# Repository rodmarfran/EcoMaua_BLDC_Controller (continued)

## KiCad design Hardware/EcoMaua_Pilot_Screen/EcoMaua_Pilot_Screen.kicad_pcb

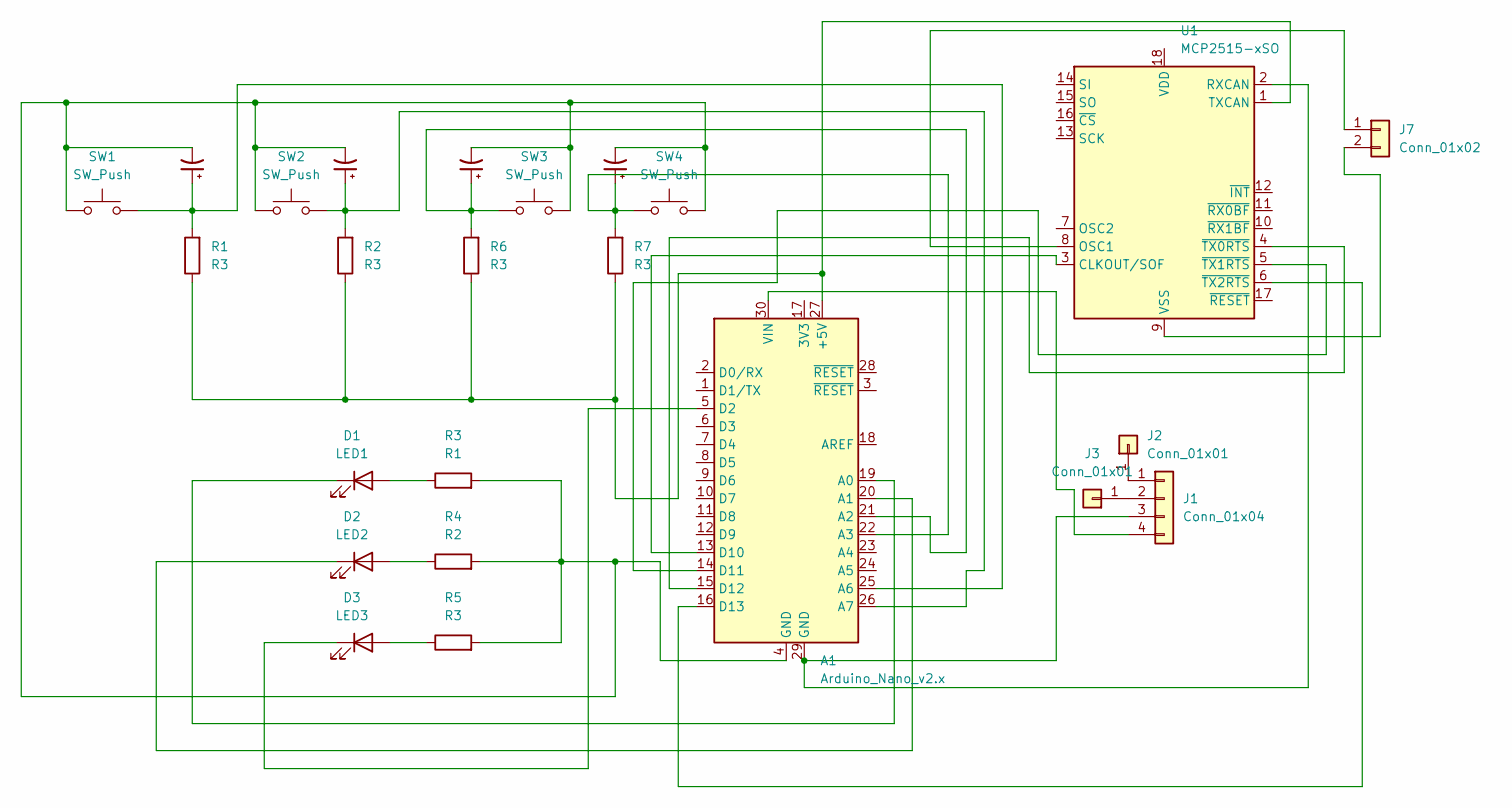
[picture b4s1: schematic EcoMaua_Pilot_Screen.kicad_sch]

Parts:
A1: Arduino_Nano_v2.x; Arduino_Nano
C1, C2, C3, C4: C_Polarized_Small_US; CP_Radial_D5.0mm_P2.50mm
D1: LED1; LED_D3.0mm
D2: LED2; LED_D3.0mm
D3: LED3; LED_D3.0mm
J1: Conn_01x04; LM2596 DC-DC HW-411
J2, J3: Conn_01x01; SolderWire-0.25sqmm_1x01_D0.65mm_OD2mm
J7: Conn_01x02; SolderWire-0.25sqmm_1x02_P4.2mm_D0.65mm_OD1.7mm
R1, R2, R5, R6, R7: R3; R_Axial_DIN0207_L6.3mm_D2.5mm_P10.16mm_Horizontal
R3: R1; R_Axial_DIN0207_L6.3mm_D2.5mm_P10.16mm_Horizontal
R4: R2; R_Axial_DIN0207_L6.3mm_D2.5mm_P10.16mm_Horizontal
SW1, SW2, SW3, SW4: SW_Push; SW_DIP_SPSTx01_Piano_10.8x4.1mm_W7.62mm_P2.54mm
U1: MCP2515-xSO; MCP2515-CANBUS MODULE FOOTPRINT

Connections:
unnamed: A1.27 (+5V), R1.1, R2.1, R6.1, R7.1, U1.1 (TXCAN)
unnamed: A1.19 (A0), D1.1 (K)
unnamed: A1.20 (A1), D2.1 (K)
unnamed: A1.21 (A2), C3.1, R6.2, SW3.1
unnamed: A1.22 (A3), C4.1, R7.2, SW4.1
unnamed: A1.25 (A6), C1.1, R1.2, SW1.2
unnamed: A1.26 (A7), C2.1, R2.2, SW2.2
unnamed: A1.5 (D2), D3.1 (K)
unnamed: A1.13 (D10), U1.3 (CLKOUT/SOF)
unnamed: A1.14 (D11), U1.5 (~TX1RTS)
unnamed: A1.15 (D12), U1.4 (~TX0RTS)
unnamed: A1.16 (D13), U1.6 (~TX2RTS)
unnamed: A1.4 (GND), C1.2, C2.2, C3.2, C4.2, R3.2, R4.2, R5.2, SW1.1, SW2.1, SW3.2, SW4.2
unnamed: A1.30 (VIN), J1.4
unnamed: D1.2 (A), R3.1
unnamed: D2.2 (A), R4.1
unnamed: D3.2 (A), R5.1
unnamed: J1.1, J2.1
unnamed: J1.2, J3.1
unnamed: A1.29 (GND), J1.3, U1.2 (RXCAN)
unnamed: J7.1, U1.8 (OSC1)
unnamed: J7.2, U1.9 (VSS)

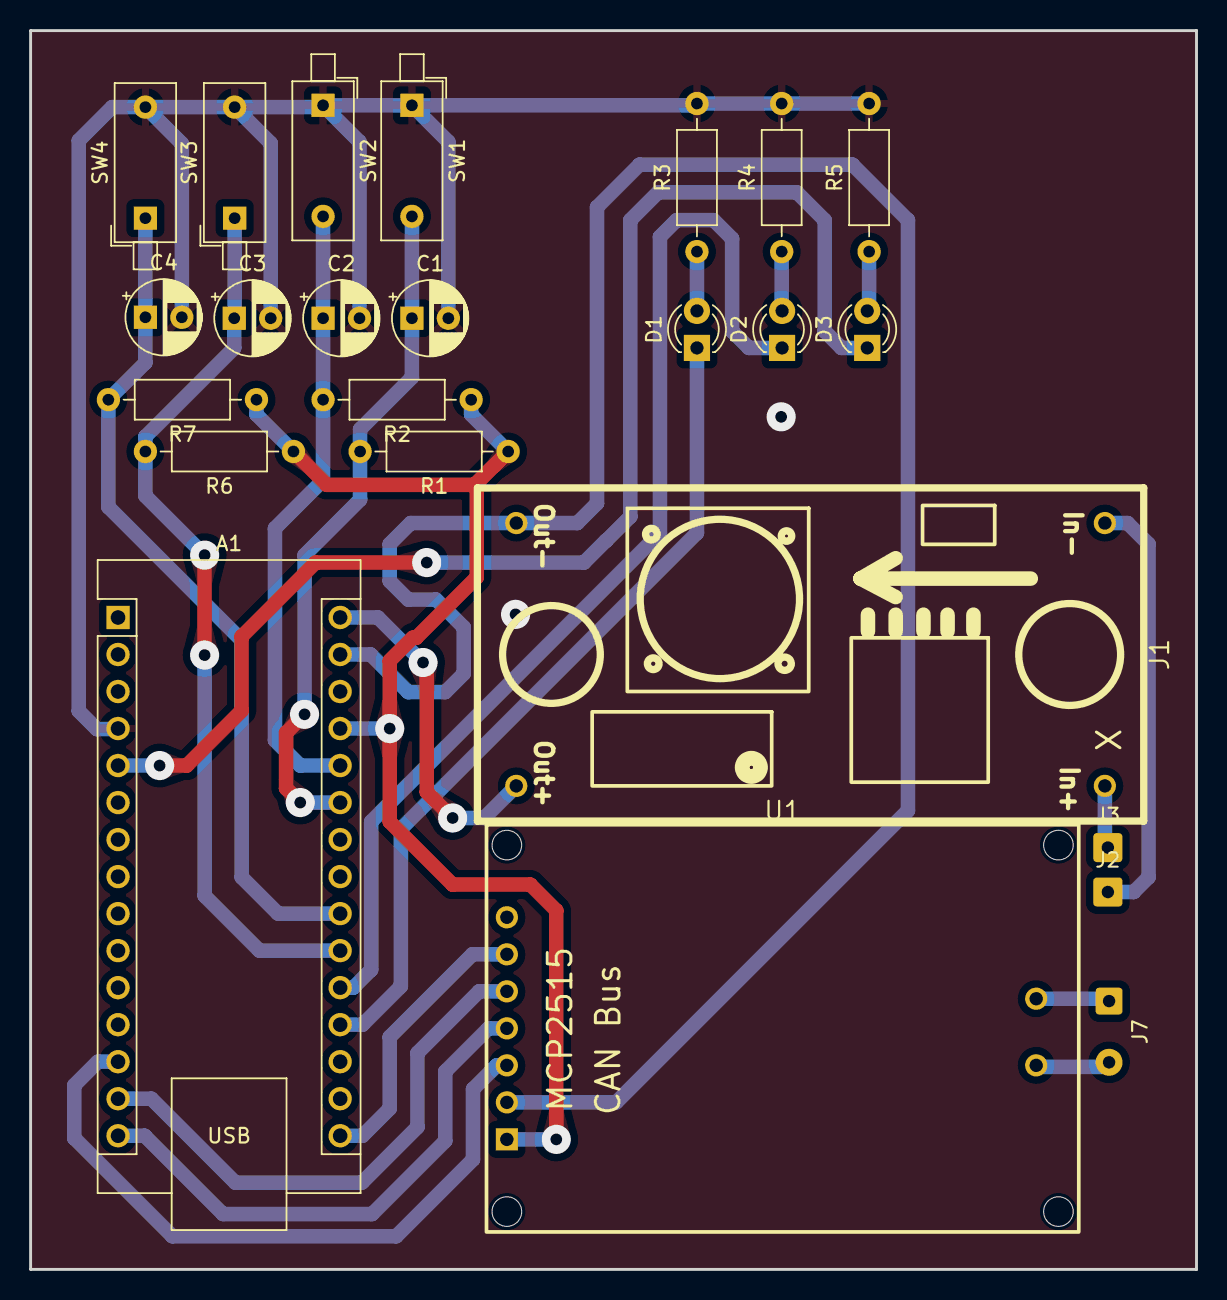
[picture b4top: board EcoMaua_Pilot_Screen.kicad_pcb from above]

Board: 2 copper layers, 80.0 x 85.0 mm, 24 parts (0 on the bottom side), 22 nets.

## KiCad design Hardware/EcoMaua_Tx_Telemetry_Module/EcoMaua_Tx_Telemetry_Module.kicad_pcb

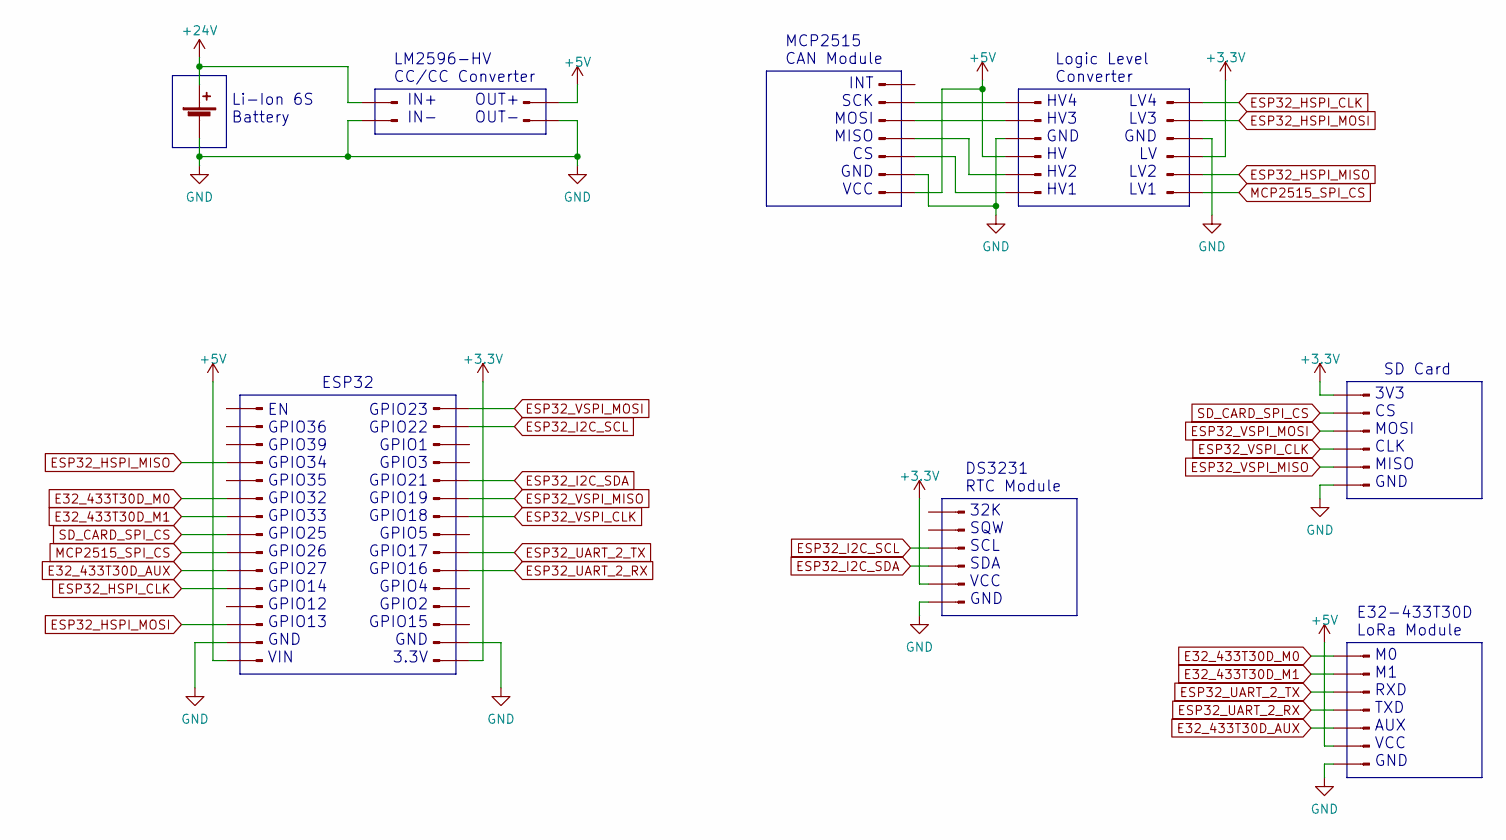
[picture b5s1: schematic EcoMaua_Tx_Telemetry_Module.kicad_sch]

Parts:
BT1: Li-Ion 6S Battery; PinHeader_1x02_P2.54mm_Vertical
J1, J3: Conn_01x15_Pin; PinHeader_1x15_P2.54mm_Vertical
J2, J4: Conn_01x02_Pin; PinHeader_1x02_P2.54mm_Vertical
J5, J10: Conn_01x07_Pin; PinSocket_1x07_P2.54mm_Vertical
J6, J7, J8, J9: Conn_01x06_Pin; PinHeader_1x06_P2.54mm_Vertical

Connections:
+3.3V: J3.15, J6.2, J8.4, J9.6
+5V: J1.1, J4.1, J5.7, J7.3, J10.2
+24V: BT1.1 (+), J2.2
E32_433T30D_AUX: J1.6, J10.3
E32_433T30D_M0: J1.10, J10.7
E32_433T30D_M1: J1.9, J10.6
ESP32_HSPI_CLK: J1.5, J8.1
ESP32_HSPI_MISO: J1.12, J8.5
ESP32_HSPI_MOSI: J1.3, J8.2
ESP32_I2C_SCL: J3.2, J6.4
ESP32_I2C_SDA: J3.5, J6.3
ESP32_UART_2_RX: J3.10, J10.4
ESP32_UART_2_TX: J3.9, J10.5
ESP32_VSPI_CLK: J3.7, J9.3
ESP32_VSPI_MISO: J3.6, J9.2
ESP32_VSPI_MOSI: J3.1, J9.4
GND: BT1.2 (-), J1.2, J2.1, J3.14, J4.2, J5.6, J6.1, J7.4, J8.3, J9.1, J10.1
MCP2515_SPI_CS: J1.7, J8.6
unnamed: J5.2, J7.6
unnamed: J5.3, J7.5
unnamed: J5.4, J7.2
unnamed: J5.5, J7.1
SD_CARD_SPI_CS: J1.8, J9.5

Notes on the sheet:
IN+ IN-
HV4 HV3 GND HV HV2 HV1
OUT+ OUT-
ESP32
MCP2515 CAN Module
Logic Level Converter
32K SQW SCL SDA VCC GND
3V3 CS MOSI CLK MISO GND
LM2596-HV CC/CC Converter
Li-Ion 6S Battery
DS3231 RTC Module
LV4 LV3 GND LV LV2 LV1
SD Card
GPIO23 GPIO22 GPIO1 GPIO3 GPIO21 GPIO19 GPIO18 GPIO5 GPIO17 GPIO16 GPIO4 GPIO2 GPIO15 GND 3.3V
EN GPIO36 GPIO39 GPIO34 GPIO35 GPIO32 GPIO33 GPIO25 GPIO26 GPIO27 GPIO14 GPIO12 GPIO13 GND VIN
M0 M1 RXD TXD AUX VCC GND
E32-433T30D LoRa Module
INT SCK MOSI MISO CS GND VCC

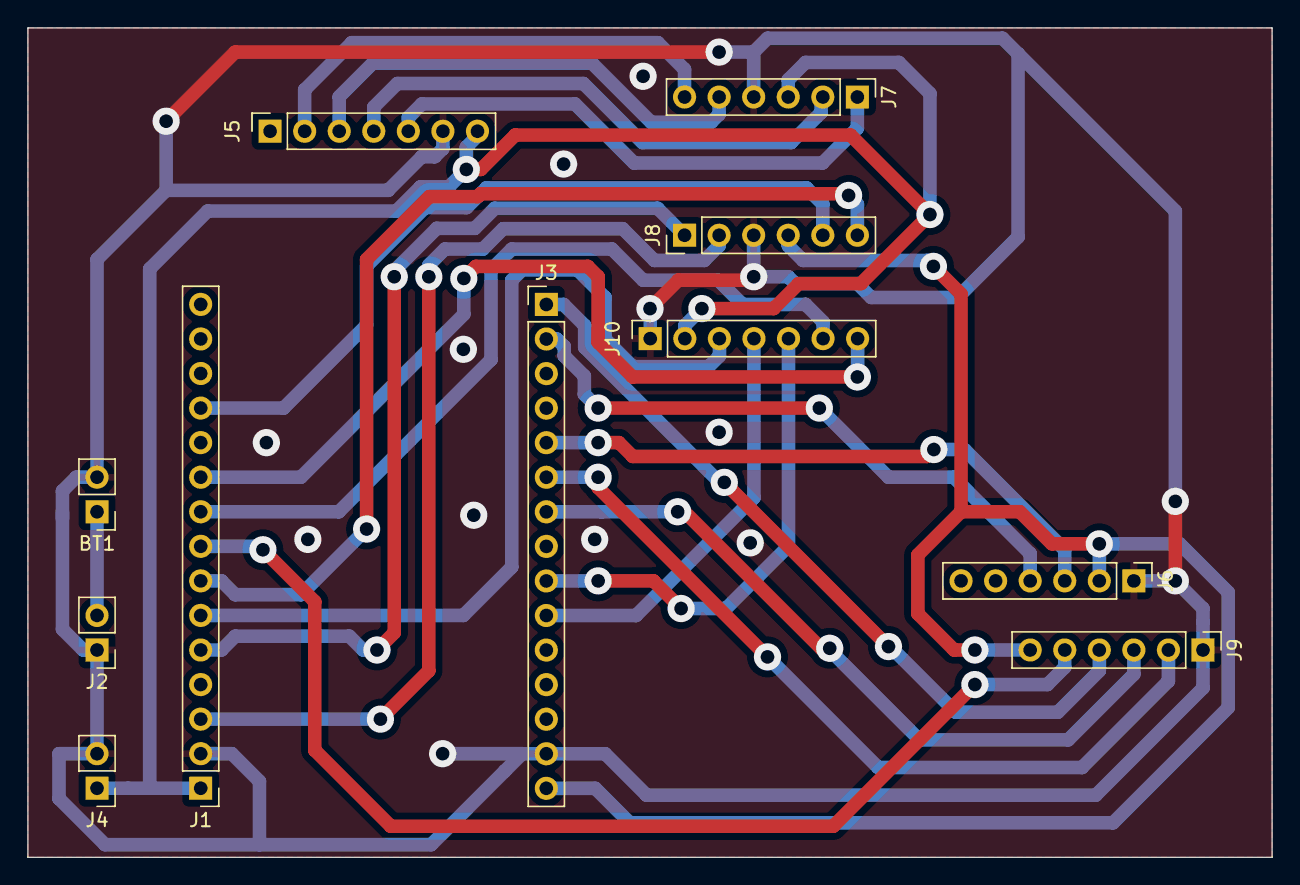
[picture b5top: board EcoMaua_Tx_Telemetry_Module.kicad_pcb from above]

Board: 2 copper layers, 91.4 x 61.0 mm, 11 parts (0 on the bottom side), 23 nets.

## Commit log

2023-07-18 Primeira versão funcional adicionada
2024-01-28 Running version
2024-01-29 Added controller comuntattion tables
2024-01-29 Ready for brushed motor open loop usage
2024-02-05 Added controller for engage motor
2024-05-06 Added CAN module and libs
2025-08-08 working version
2025-08-08 Version with CAN and correct acceleration
2025-08-08 removed external serial commands and added current stalling protection
2025-08-12 testes de elocidade concluidos com motor de cubo
2025-09-21 Final code for 2025 ShellEco Marathon competition
2025-09-21 Added others codes from the vehicle
2025-09-21 Reorganization and added documentation files
2025-09-21 Added PCB project files
2025-09-21 Added CAD Files
2025-09-21 Added Diagrams to documentation
